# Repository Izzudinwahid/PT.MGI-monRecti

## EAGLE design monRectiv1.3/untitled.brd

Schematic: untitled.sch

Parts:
C1, C2: 22pF; C0805K
C3, C4, C8, C10, C12: 100nF; C0805K
C5, C6, C7: 1uF; C0805K
C9: 10uF/16V; 153CLV-0505
C11: 10uF; C0805K
D1, D2, D3, D4, D5, D6, D7, D8, D9, D10: DIODE-SOD123; SOD123
D11, D12: 1N5819HW-7; SOD3715X145N
D13, D14, D15, D17, D18, D19, D20, D21, D22, D23, D24, D25, D26: SML-LXT0805IW-TR; LEDC2012X120N
D33, D34, D35, D36, D37, D38, D39, D40, D41, D42: US1M-13; DIOM5226X240N
IC1: MCP23017SS; SSOP28
J1: U.FL-R-SMT(01); HRS_U.FL-R-SMT(01)
J2: 10118193-0001LF; FCI_10118193-0001LF
JP1, JP2: PINHD-1X3CB; 1X03-CLEANBIG
LORA-NICERF-V1: LORA-NICERF-V2
MINI1: MINI560
PZEM-DC1, PZEM-DC2: PZEM-DC
Q1: 12MHz; SM49
Q2, Q3: MMBT3904; SOT95P240X120-3N
R1, R2, R3, R4, R5, R6, R7, R8, R9, R10: R-EU_0414/15; 0414/15
R11, R12, R13, R14, R15, R16, R27, R28, R29, R30, R31, R32: 10k; R0805
R17, R18, R19, R20, R21, R22, R23, R24, R25, R26: R-EU_R0805; R0805
R33: 330; R0805
S3, S4: TL1015AF160QG; SW_TL1015AF160QG
TTL-RS1: TTL-RS485
U1, U2, U3, U4, U5, U6, U7, U8, U9, U10: PC817X2NIP0F; SOT254P975X400-4N
U11: ADS1115IDGSR; SOP50P490X110-10N
U12: CH340G; SOIC127P600X180-16N
U13: ESP32-WROOM-32D; MODULE_ESP32-WROOM-32D
U14: AMS1117; SOT229P700X180-4N
U$1: MINI_W5500
X1, X2: MSTBA5
X4: MSTBA4
X5, X6, X9: MSTBA3
X7, X8: MSTBA2

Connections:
3V3: C6.2, C11.1, C12.1, LORA-NICERF-V1.VCC, R27.2, R28.2, R31.2, R32.2, U13.2 (3V3), U14.2 (VOUT), U14.4 (VOUT)
12V: JP1.3, MINI1.IN+, X5.1, X6.1
A0: U11.4 (AIN0), X5.2
A1: U11.5 (AIN1), X6.2
A+: PZEM-DC1.A+, PZEM-DC2.A+, TTL-RS1.A, X4.3
ANT: J1.3 (SIG), LORA-NICERF-V1.ANT
B-: PZEM-DC1.B-, PZEM-DC2.B-, TTL-RS1.B, X4.2
COMM: D1.A, D2.A, D3.A, D4.A, D5.A, D6.A, D7.A, D8.A, D9.A, D10.A, U1.2 (C), U2.2 (C), U3.2 (C), U4.2 (C), U5.2 (C), U6.2 (C), U7.2 (C), U8.2 (C), U9.2 (C), U10.2 (C), X9.1
DIO0_LORA: LORA-NICERF-V1.DIO0, U13.10 (IO25)
DIO1_LORA: LORA-NICERF-V1.DIO1, U13.11 (IO26)
DTR: Q3.2 (E), R29.2, U12.13 (!DTR)
EN: C3.1, Q2.3 (C), R27.1, S3.1, U13.3 (EN)
GND: C1.1, C2.1, C3.2, C4.2, C5.1, C6.1, C7.2, C8.2, C9.-, C10.1, C11.2, C12.2, D13.C, IC1.10 (VSS), J1.1 (GND), J1.2 (GND), J2.5 (GND), J2.S1 (SHIELD), J2.S2 (SHIELD), J2.S3 (SHIELD), J2.S4 (SHIELD), J2.S5 (SHIELD), J2.S6 (SHIELD), JP1.1, LORA-NICERF-V1.GND, LORA-NICERF-V1.GND1, MINI1.IN-, MINI1.OUT-, PZEM-DC1.GND, PZEM-DC1.GND1, PZEM-DC2.GND, PZEM-DC2.GND1, R13.1, R14.1, R15.1, S3.2, S4.2, TTL-RS1.GND, U1.3 (ET), U2.3 (ET), U3.3 (ET), U4.3 (ET), U5.3 (ET), U6.3 (ET), U7.3 (ET), U8.3 (ET), U9.3 (ET), U10.3 (ET), U11.1 (ADDR), U11.3 (GND), U12.1 (GND), U13.1 (GND), U13.15 (GND), U13.38 (GND), U13.39_1 (GND), U13.39_2 (GND), U13.39_3 (GND), U13.39_4 (GND), U13.39_5 (GND), U13.39_6 (GND), U13.39_7 (GND), U13.39_8 (GND), U13.39_9 (GND), U13.39_10 (GND), U13.39_11 (GND), U13.39_12 (GND), U13.39_13 (GND), U13.39_14 (GND), U13.39_15 (GND), U13.39_16 (GND), U13.39_17 (GND), U13.39_18 (GND), U13.39_19 (GND), U13.39_20 (GND), U13.39_21 (GND), U14.1 (ADJ/GND), U$1.GND, U$1.GND.2, U$1.GND.3, X4.4, X5.3, X6.3
IO0: C4.1, Q3.3 (C), R28.1, S4.1, U13.25 (IO0)
LED_PRS: U13.12 (IO27)
LED_WRN: U13.8 (IO32)
MISO_HSPI: LORA-NICERF-V1.MISO, U13.14 (IO12)
MISO_LAN: U13.31 (IO19), U$1.MISO
MOSI_HSPI: LORA-NICERF-V1.MOSI, U13.16 (IO13)
MOSI_LAN: U13.37 (IO23), U$1.MOSI
unnamed: D17.A, D33.C (K)
unnamed: D33.A, R1.2
unnamed: D1.C, D17.C, U1.1 (A)
unnamed: JP2.3, X9.3
unnamed: D34.A, R2.2
unnamed: D18.A, D34.C (K)
unnamed: D2.C, D18.C, U2.1 (A)
unnamed: D35.A, R3.2
unnamed: D19.A, D35.C (K)
unnamed: D3.C, D19.C, U3.1 (A)
unnamed: D36.A, R4.2
unnamed: D20.A, D36.C (K)
unnamed: D4.C, D20.C, U4.1 (A)
unnamed: JP2.1, X9.2
unnamed: D11.A, MINI1.OUT+
unnamed: D13.A, R33.1
unnamed: D37.A, R5.2
unnamed: D21.A, D37.C (K)
unnamed: D5.C, D21.C, U5.1 (A)
unnamed: D38.A, R6.2
unnamed: D22.A, D38.C (K)
unnamed: D6.C, D22.C, U6.1 (A)
unnamed: IC1.18 (!RESET), R16.2
unnamed: C8.1, U12.4 (V3)
unnamed: D39.A, R7.2
unnamed: D23.A, D39.C (K)
unnamed: D7.C, D23.C, U7.1 (A)
unnamed: D40.A, R8.2
unnamed: D24.A, D40.C (K)
unnamed: D8.C, D24.C, U8.1 (A)
unnamed: IC1.15 (A0), R13.2
unnamed: D41.A, R9.2
unnamed: D25.A, D41.C (K)
unnamed: D9.C, D25.C, U9.1 (A)
unnamed: D42.A, R10.2
unnamed: D26.A, D42.C (K)
unnamed: D10.C, D26.C, U10.1 (A)
unnamed: IC1.16 (A1), R14.2
unnamed: IC1.17 (A2), R15.2
unnamed: D14.A, R31.1
unnamed: D15.A, R32.1
unnamed: Q2.1 (B), R29.1
unnamed: Q3.1 (B), R30.1
unnamed: C1.2, Q1.2, U12.7 (XI)
unnamed: C2.2, Q1.1, U12.8 (XO)
OUT1: IC1.21 (GPA0), R17.2, U1.4 (CT)
OUT2: IC1.22 (GPA1), R18.2, U2.4 (CT)
OUT3: IC1.23 (GPA2), R19.2, U3.4 (CT)
OUT4: IC1.24 (GPA3), R20.2, U4.4 (CT)
OUT5: IC1.25 (GPA4), R21.2, U5.4 (CT)
OUT6: IC1.26 (GPA5), R22.2, U6.4 (CT)
OUT7: IC1.27 (GPA6), R23.2, U7.4 (CT)
OUT8: IC1.28 (GPA7), R24.2, U8.4 (CT)
OUT9: IC1.1 (GPB0), R25.2, U9.4 (CT)
OUT10: IC1.2 (GPB1), R26.2, U10.4 (CT)
P1: R1.1, X1.1
P2: R2.1, X1.2
P3: R3.1, X1.3
P4: R4.1, X1.4
P5: R5.1, X1.5
P6: R6.1, X2.5
P7: R7.1, X2.4
P8: R8.1, X2.3
P9: R9.1, X2.2
P10: R10.1, X2.1
RST_LORA: LORA-NICERF-V1.NRST, U13.23 (IO15)
RTS: Q2.2 (E), R30.2, U12.14 (!RTS)
RX: D15.C, U12.3 (RXD), U13.35 (TXD0)
RX_RS485: TTL-RS1.RX, U13.28 (IO17)
SCK_HSPI: LORA-NICERF-V1.SCK, U13.13 (IO14)
SCK_LAN: U13.30 (IO18), U$1.SCLK
SCL: IC1.12 (SCL), R11.2, U11.10 (SCL), U13.36 (IO22)
SDA: IC1.13 (SDA), R12.2, U11.9 (SDA), U13.33 (IO21)
SS_LAN: U13.29 (IO5), U$1.CS
SS_LORA: LORA-NICERF-V1.NSS, U13.26 (IO4)
TX: D14.C, U12.2 (TXD), U13.34 (RXD0)
TX_RS485: TTL-RS1.TX, U13.27 (IO16)
USB_N: J2.2 (D-), U12.6 (UD-)
USB_P: J2.3 (D+), U12.5 (UD+)
VCC: C5.2, C10.2, D11.C (K), D12.C (K), IC1.9 (VDD), PZEM-DC1.5V, PZEM-DC1.VCC1, PZEM-DC2.5V, PZEM-DC2.VCC1, R11.1, R12.1, R16.1, R17.1, R18.1, R19.1, R20.1, R21.1, R22.1, R23.1, R24.1, R25.1, R26.1, R33.2, TTL-RS1.VCC, U11.8 (VDD), U14.3 (VIN), U$1.3V3, U$1.3V3.2, X4.1
VOLT1+: PZEM-DC1.VDC+ (+VDC), X7.1
VOLT1-: PZEM-DC1.VDC- (-VDC), X7.2
VOLT2+: PZEM-DC2.VDC+ (+VDC), X8.1
VOLT2-: PZEM-DC2.VDC- (-VDC), X8.2
VUSB: C7.1, C9.+, D12.A, J2.1 (VUSB), U12.16 (VCC)

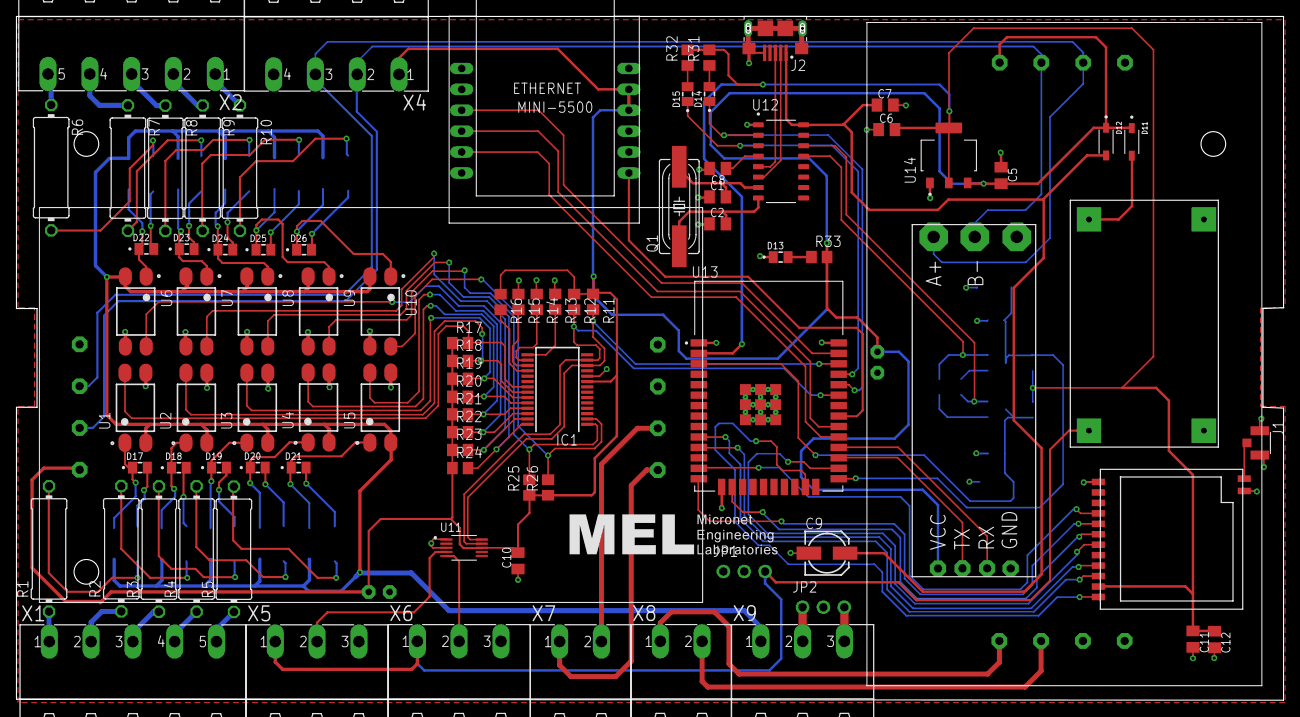
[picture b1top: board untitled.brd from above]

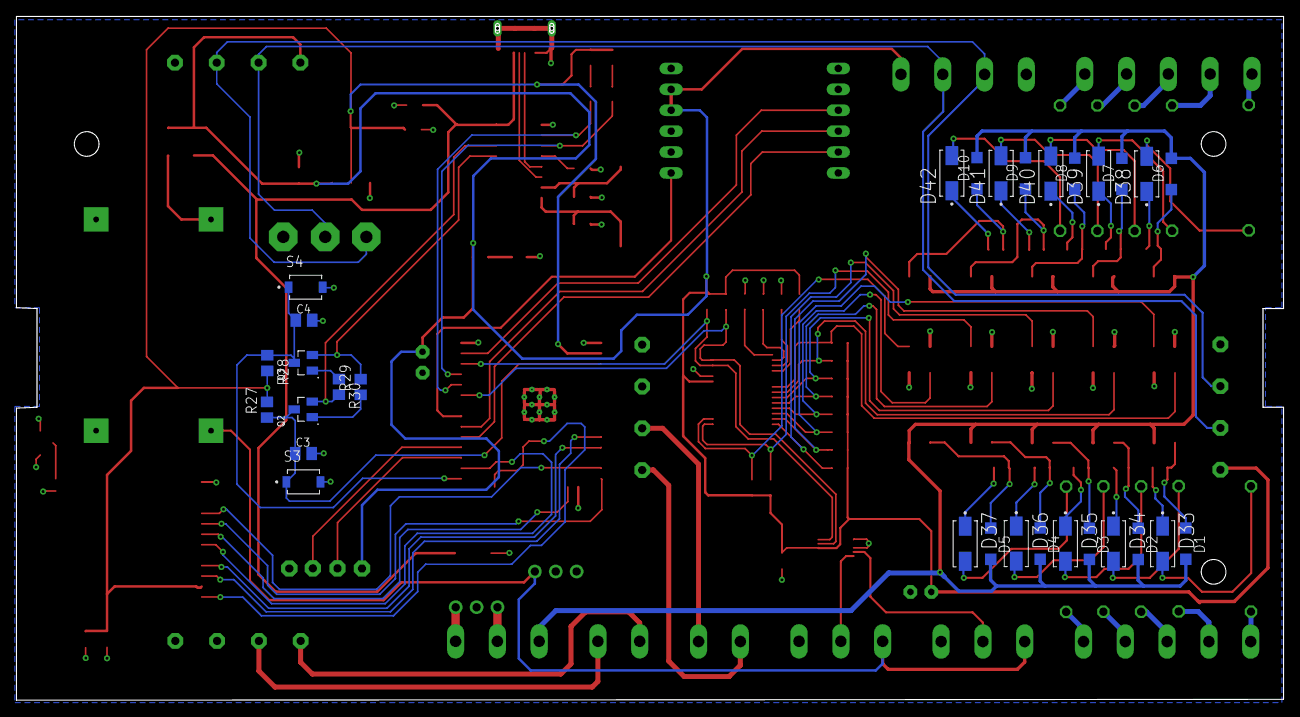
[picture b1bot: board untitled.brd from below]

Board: 2 copper layers, 154.0 x 83.1 mm, 118 parts (30 on the bottom side), 103 nets.

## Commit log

2022-09-26 membuat desain PCB monRecti
2022-09-28 revisi rangkaian
2022-11-25 penambahan firmware
2023-06-27 fix tanggal 27/06/2023
2023-06-27 PCB monrecti v1.2
2024-08-09 revisi PCBv1.3
